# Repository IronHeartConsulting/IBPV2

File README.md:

IBPV2
=====

*DRAFT*

International Beacon Program - V2.0

http://www.ncdxf.org/pages/beacons.html
http://www.ncdxf.org/beacon/schematic.pdf
http://www.ncdxf.org/beacon/source.txt

The purpose of the NCDXF/IARU HF Beacon is to allow worldwide amateur
radio operators to judge HF propagation at your location, for your
local time.  To use it, tune in the beacons, and if you can hear a
beacon, you might be able to work some HF DX to that area of the
world.

The v1.0 beacon equipment consists of a HF Vertical antenna, Kenwood TS50
transceiver, a Trimble Acutime GPS unit, and a custom controller built
around a 8748 micro controller.

The network has been on the air for about 10 years. The current
problem is the equipment is getting old, and dying.  The original
designers never expected the units to remain in the field 10 years.

# HF V2.0 Beacon Network 

The goal is to design a replacement equipment package that duplicates
the existing features.  There has been a lot of proposals for more
features, other ways, etc.  But, none of those proposing have been
willing to put any work into it.

The aim is a practical design, with few or no new features.

# Equipment 

## Minimum Equipment
- ICOM IC-7200 Transceiver
- New TX Antenna
- GPS
- Switches
- LCD
- Rig Interface board
- Power Supply
- Filtering and isolation
- Chassis

## Additional possibilities
- Backup RTC with TXC (DS3231 or http://www.adafruit.com/products/255)
- Network: WiFi or Ethernet for command & control, status

# Functionality 

Each beacon transmits every three minutes, day and night.

A transmission consists of the callsign of the beacon sent at 22 words
per minute followed by four one-second dashes. The callsign and the
first dash are sent at 100 watts. The remaining dashes are sent at 10
watts, 1 watt and 100 milliwatts.

The beacons cycle thru the bands 14 Mhz, 18 MHz, 21 MHz, 24 MHz and 28 MHz.

Each station is given a specific time slot, such that only one
frequency is needed (on 20m, it’s 14.100).  The unit uses GPS to get
an accurate time, to synchronize it’s timeslot.  The beacon transmits
on each band for ten seconds, once every three minutes.

- Check switch for test sqeuence.
- Monitor the GPS unit - get the current time of day, and monitor the 1PPS signal.  
- Compute the correct timeslot for the station
- Check switches for band enable/disable.
- Send commands via  CI-V / CAT to the radio to select the frequency, and power level via commands
- Send the callsign and long dashes in CW.

This table gives the minute and second of the start of the first
transmission within the hour for each beacon on each frequency, and
reports the status.

http://www.ncdxf.org/beacon/beaconschedule.html

## Test Mode

Below is the v1.0 test mode

The test sequence is used for adjusting the power levels and checking
the keying waveforms.  Control the power level and request
either a string of dots or continual keying by using the switches
which normally disable particular bands:

| Effect    | Switch  |
| --------- | ------- |
| 100 watts | 28 MHz  |
| 10 watts  | 24 MHz  |
| 1 watt    | 21 MHz  |
| 0.1 watt  | 18 MHz  |
| Dits      | 14 MHz  |
| Carrier   | 10 MHz  |

# Equipment and Components Details 

## ICOM IC-7200 Transceiver

The ICOM IC-7200 transceiver offers CI-V commands for control of frequency, transmissions, and for monitoring.

For the CI-V commands see: http://www.plicht.de/ekki/civ/civ-p4.html

Statistics could also be gathered: for example, SWR could be measured.

## New TX Antenna

There is likely no impact of antenna choice on this part of the v2.0 beacon project.

## GPS

The GPS data stream will tell us the correct time of day.  Once we
know that, and our slot ID, we can just init a countdown register to
our time slot.

## Switches

The v1.0 system has the following switches:

- Band Switches (6)
- Test Switches (1 used, 3 reserved)

The band switches control which bands are used.  v1.0 covers 5 bands
with a 6th slot reserved for 10 MHz.

One test switch controls test mode, and in test mode, the band switches
have other functions.  Three other switches are reserved.

## LCD

The v1.0 system has a single LED for showing GPS and other status.

Switching to a small LCD character display will make operation easier
and will not greatly increase cost.  An i2c LCD is probably the best
choice.  

There are combination switch/LCD I2C products that we can use and
avoid the switch overloading by using screen feedback.  For example,
http://www.adafruit.com/products/772

Or we could use the Akafugu LCD backpack and use a separate mechanism for
switches.  This product has the advantage that it is mechanically easier
to mount in case.  https://store.akafugu.jp/products/26

## Arduino

- The Arduino Uno will be standard and remain easily understood for years.
- The Arduino Leonardo has the advantage of a separate programming port and hardware TTL port for the GPS.  Software TTL for CI-V rig control.
- The Arduino Mega has the disadvantage of being off the Arduino main line, and users often have trouble with support for hardware and libraries.
- The Arduino Yun is a combination of the Arduino Leonardo, a small Linux system running OpenWRT, and integrated Wifi connection, and an Ethernet connection.

Tentative Recommendations:
- The Arduino Leonardo is probably the best choice for the non-network version
- The Arduino Yun is the best choice for the connected version.

## Interface Board

The interface board is an Arduino Shield.  It has headers for
connections to the IC-7200 CI-V TTL serial, IC-7200 CW line, GPS TTL
serial, LCD, and possibly RTC.

## Optional item: Network: WiFi or Ethernet for command & control, status

The sites are mostly hosted.  If we had a USB connection to a local
PC, then we could send the host a file to load new code on the
controller, and we could also collect stats, etc.

If there is a network (WiFi or wired) we could also report the statistics,
such as whether it's online, what the SWR is.

## Optional item: Backup RTC with TXC

It might be nice to include a quartz crystal based time module, to
keep it disciplined with the GPS, in case there is some loss of GPS
signal.

Backup disciplined clock for use when GPS isn't available, for example, indoors.

- DS3231 board
- http://www.adafruit.com/products/255

# Engineering Resources 

- Project Management: Kevin K6TD
- Arduino system: Leigh WA5ZNU
- Rig Control: Kevin K6TD
- Beacon Event Loop: Leigh WA5ZNU
- UX: ?
- Systems Design: Kevin K6TD
- Hardware Design: Kevin K6TD
- Testing: ?

May 15, 2015
# libraries used
SoftSerial
AdaFruit_GPS
EnableInterrupt
LCDi2cNHD
arduinomorse

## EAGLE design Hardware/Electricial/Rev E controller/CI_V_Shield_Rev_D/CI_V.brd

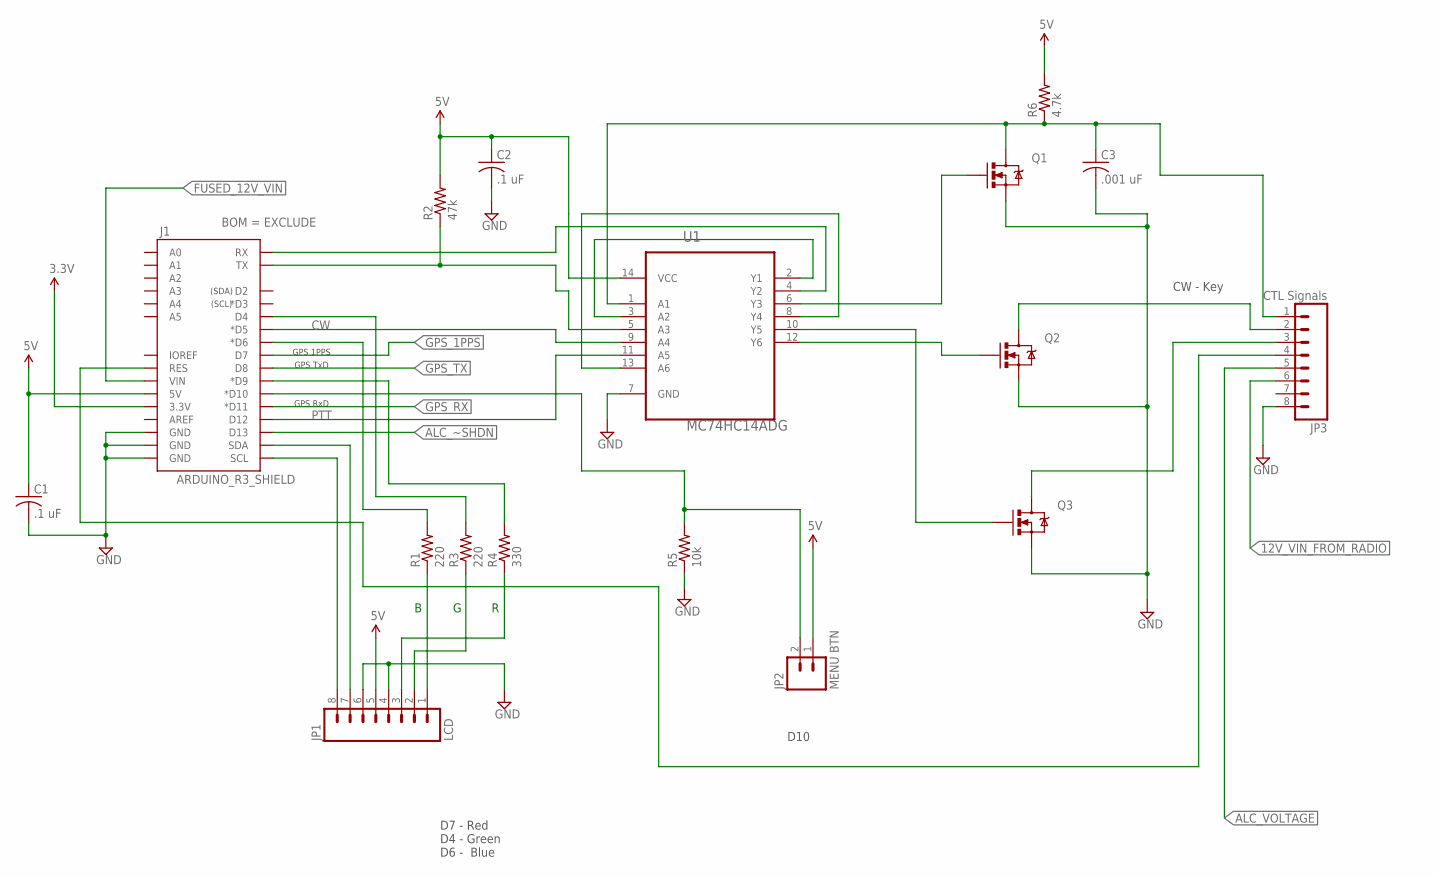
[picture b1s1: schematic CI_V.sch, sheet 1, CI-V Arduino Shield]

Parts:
C1, C2: .1 uF; C0805; PARTNO 120-0001-010
C3: .001 uF; C0805; PARTNO 120-0001-015
J1: ARDUINO_R3_SHIELD; UNO_R3_SHIELD
JP1: LCD; 1X08_PIN1_NO_SILK; PARTNO 125-0019-001
JP2: MENU BTN; 1X02; PARTNO 125-0019-001
JP3: CTL Signals; 1X08_PIN1_NO_SILK; PARTNO 125-0019-001
Q1, Q2, Q3: MOSFET-NCHANNELBSS123LT1G; SOT23-3; PARTNO 185-0001-001
R1, R3: 220; R0805; PARTNO 110-0001-010
R2: 47k; R0805; PARTNO 110-0001-030
R4: 330; R0805; PARTNO 110-0001-025
R5: 10k; R0805; PARTNO 110-0001-025
R6: 4.7k; R0805; PARTNO 110-0001-030
U1: MC74HC14ADG; SOIC127P600X175-14N; PARTNO 200-0001-001

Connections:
3.3V: J1.3.3V; also elsewhere on the board
5V: C1.1, C2.1, J1.5V, JP1.5, JP2.1, R2.2, R6.2, U1.14 (VCC); also elsewhere on the board
12V_VIN_FROM_RADIO: JP3.6; also elsewhere on the board
ALC_VOLTAGE: JP3.5; also elsewhere on the board
ALC_~SHDN: J1.D13; also elsewhere on the board
CW: J1.D5 (*D5), U1.9 (A4)
FUSED_12V_VIN: J1.VIN; also elsewhere on the board
GND: C1.2, C2.2, C3.2, J1.GND@0 (GND), J1.GND@1 (GND), J1.GND@2 (GND), JP1.4, JP1.6, JP3.8, Q1.2 (S), Q2.2 (S), Q3.2 (S), R5.1, U1.7 (GND); also elsewhere on the board
GPS_1PPS: J1.D7; also elsewhere on the board
GPS_RX: J1.D11 (*D11); also elsewhere on the board
GPS_TX: J1.D8; also elsewhere on the board
HARD_RX: J1.RX, U1.4 (Y2)
HARD_TX: J1.TX, R2.1, U1.5 (A3)
unnamed: C3.1, JP3.1, Q1.3 (D), R6.1, U1.1 (A1)
unnamed: JP3.2, Q2.3 (D)
unnamed: JP3.3, Q3.3 (D)
unnamed: Q1.1 (G), U1.6 (Y3)
unnamed: JP1.1, R1.1
unnamed: JP1.2, R3.1
unnamed: U1.2 (Y1), U1.3 (A2)
unnamed: Q2.1 (G), U1.12 (Y6)
unnamed: Q3.1 (G), U1.10 (Y5)
unnamed: J1.SCL, JP1.8
unnamed: U1.8 (Y4), U1.13 (A6)
unnamed: J1.SDA, JP1.7
unnamed: JP1.3, R4.1
unnamed: J1.D6 (*D6), R1.2
unnamed: J1.D4, R3.2
unnamed: J1.D9 (*D9), R4.2
unnamed: J1.D10 (*D10), JP2.2, R5.2
unnamed: J1.RES, JP3.4
PTT: J1.D12, U1.11 (A5)

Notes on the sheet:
CW - Key
D7 - Red D4 - Green D6 - Blue
D10
GPS TxD
GPS RxD
GPS 1PPS

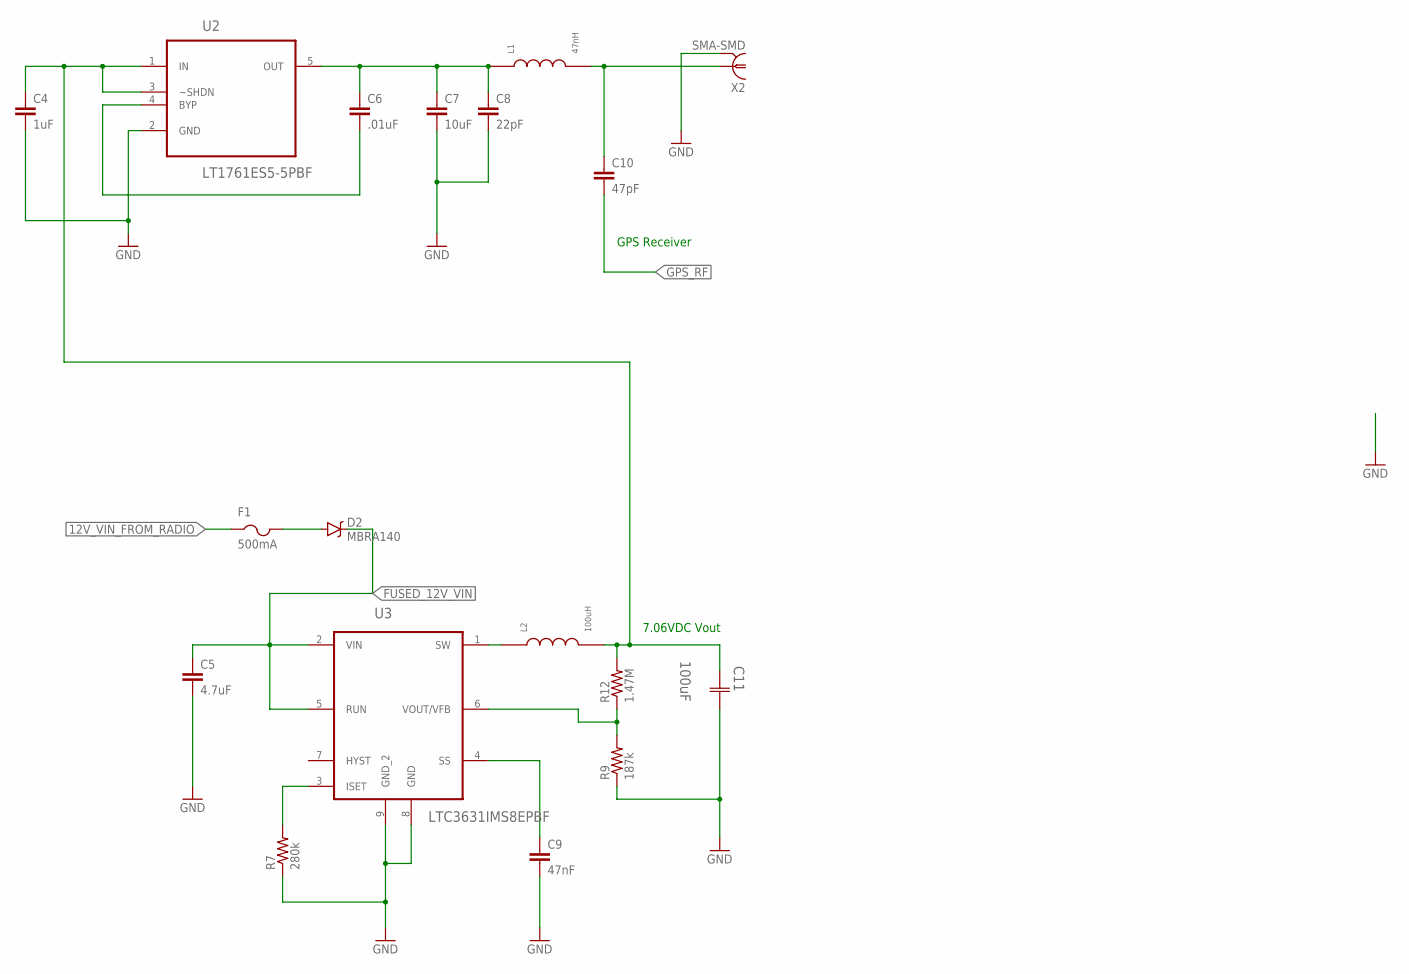
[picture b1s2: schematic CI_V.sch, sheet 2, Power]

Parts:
C4: 1uF; 0805; PARTNO 120-0001-015
C5: 4.7uF; 1210; PARTNO 120-0003-011
C6: .01uF; 0805; PARTNO 120-0001-020
C7: 10uF; 1210; PARTNO 120-0003-010
C8: 22pF; 0805; PARTNO 120-0004-011
C9: 47nF; 0805; PARTNO 120-0001-013
C10: 47pF; 0805; PARTNO 120-0004-010
C11: 100uF; CAPCP6032X280N; PARTNO 120-0005-050
D2: MBRA140; SMA-DIODE; PARTNO 140-0001-001
F1: 500mA; R1206; PARTNO 145-0001-001
L1: 47nH; 0805; PARTNO 155-0002-001
L2: 100uH; SLF7045; PARTNO 155-0001-001
R7: 280k; 0805; PARTNO 110-0002-015
R9: 187k; 0805; PARTNO 110-0002-020
R12: 1.47M; 0805; PARTNO 110-0002-010
U2: LT1761ES5-5PBF; SOT95P280X100-5N; PARTNO 230-0002-001
U3: LTC3631IMS8EPBF; SOP65P490X110-9N; PARTNO 230-0003-001
X2: SMA-SMD; PARTNO 125-0018-001

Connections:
7V_BUS: C4.1, C11.1 (C1), L2.2, R12.2, U2.1 (IN), U2.3 (~SHDN)
12V_VIN_FROM_RADIO: F1.1; also elsewhere on the board
FUSED_12V_VIN: C5.1, D2.C, U3.2 (VIN), U3.5 (RUN); also elsewhere on the board
GND: C4.2, C5.2, C7.2, C8.2, C9.2, C11.2 (C2), R7.1, R9.1, U2.2 (GND), U3.8 (GND), U3.9 (GND_2), X2.2@1 (2), X2.2@2 (2), X2.2@3 (2), X2.2@4 (2), X2.2@5 (2), X2.2@6 (2); also elsewhere on the board
GPS_RF: C10.2; also elsewhere on the board
ISET: R7.2, U3.3 (ISET)
unnamed: C10.1, L1.2, X2.1
unnamed: C6.2, U2.4 (BYP)
unnamed: D2.A, F1.2
SS: C9.1, U3.4 (SS)
SW: L2.1, U3.1 (SW)
VCC: C6.1, C7.1, C8.1, L1.1, U2.5 (OUT)
VFB: R9.2, R12.1, U3.6 (VOUT/VFB)

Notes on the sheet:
GPS Receiver
7.06VDC Vout

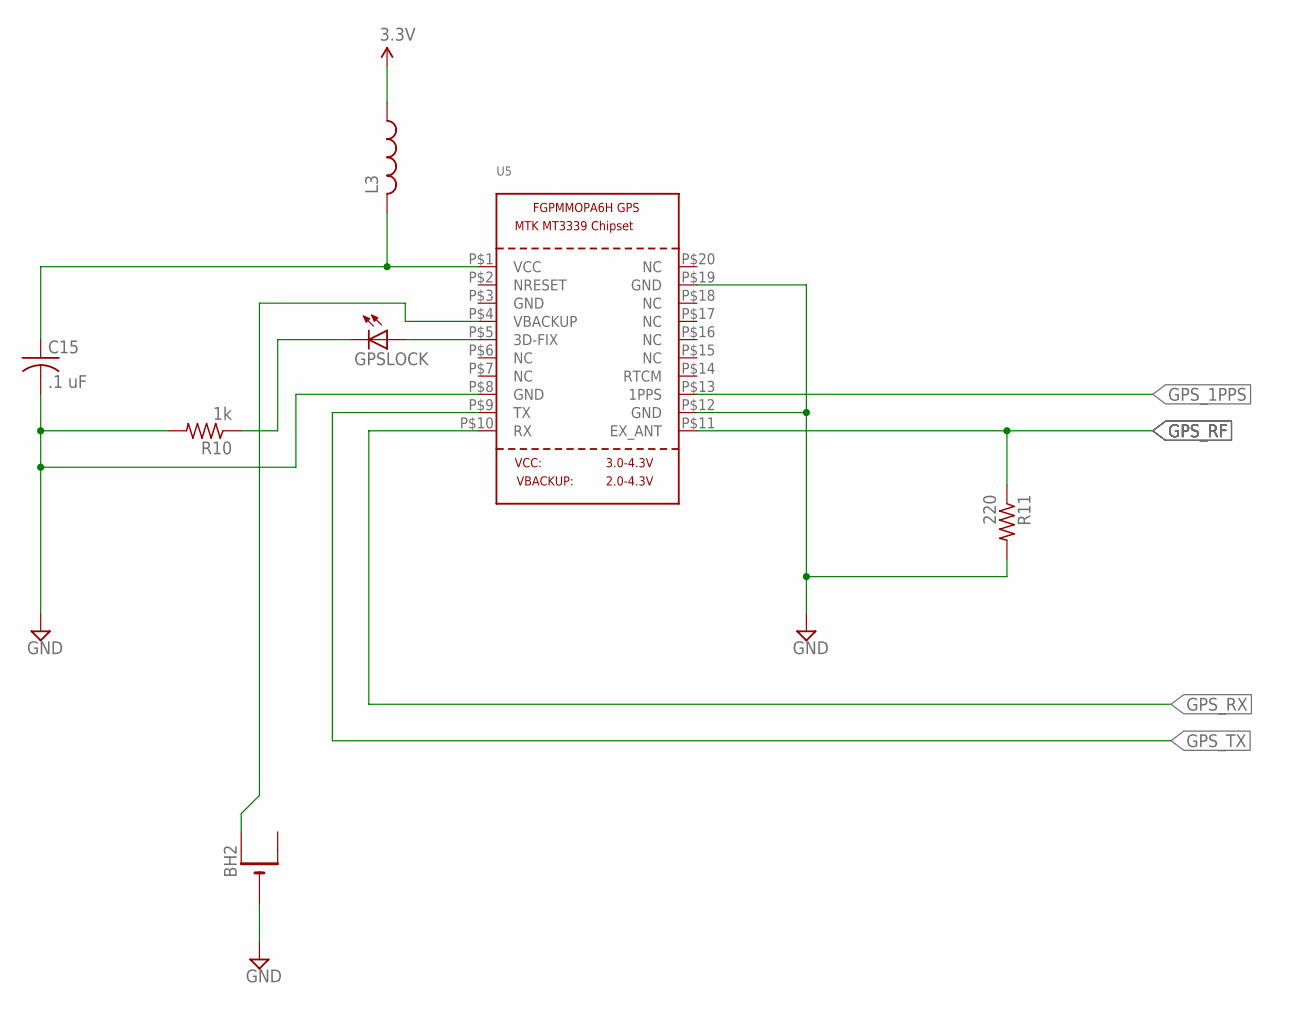
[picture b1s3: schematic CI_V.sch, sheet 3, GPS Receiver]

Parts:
BH2: CR1220SMT; CR1220-SMD; PARTNO 165-0001-001
C15: .1 uF; C0805; PARTNO 120-0001-010
GPSLOCK: LEDCHIPLED_0805; CHIPLED_0805; PARTNO 160-0007-001
L3: L-USL2012C; L2012C; PARTNO 155-0004-001
R10: 1k; R0805; PARTNO 110-0001-029
R11: 220; R0805; PARTNO 110-0001-010
U5: GPS_FGPMMOPA6H; FGPMMOPA6H; PARTNO 240-0001-001

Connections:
3.3V: L3.1; also elsewhere on the board
GND: BH2.-, C15.2, R10.2, R11.2, U5.P$8 (GND), U5.P$12 (GND), U5.P$19 (GND); also elsewhere on the board
GPS_1PPS: U5.P$13 (1PPS); also elsewhere on the board
GPS_BATT: BH2.+$1 (+), U5.P$4 (VBACKUP)
GPS_RF: R11.1, U5.P$11 (EX_ANT); also elsewhere on the board
GPS_RX: U5.P$10 (RX); also elsewhere on the board
GPS_TX: U5.P$9 (TX); also elsewhere on the board
unnamed: C15.1, L3.2, U5.P$1 (VCC)
unnamed: GPSLOCK.A, U5.P$5 (3D-FIX)
unnamed: GPSLOCK.C, R10.1

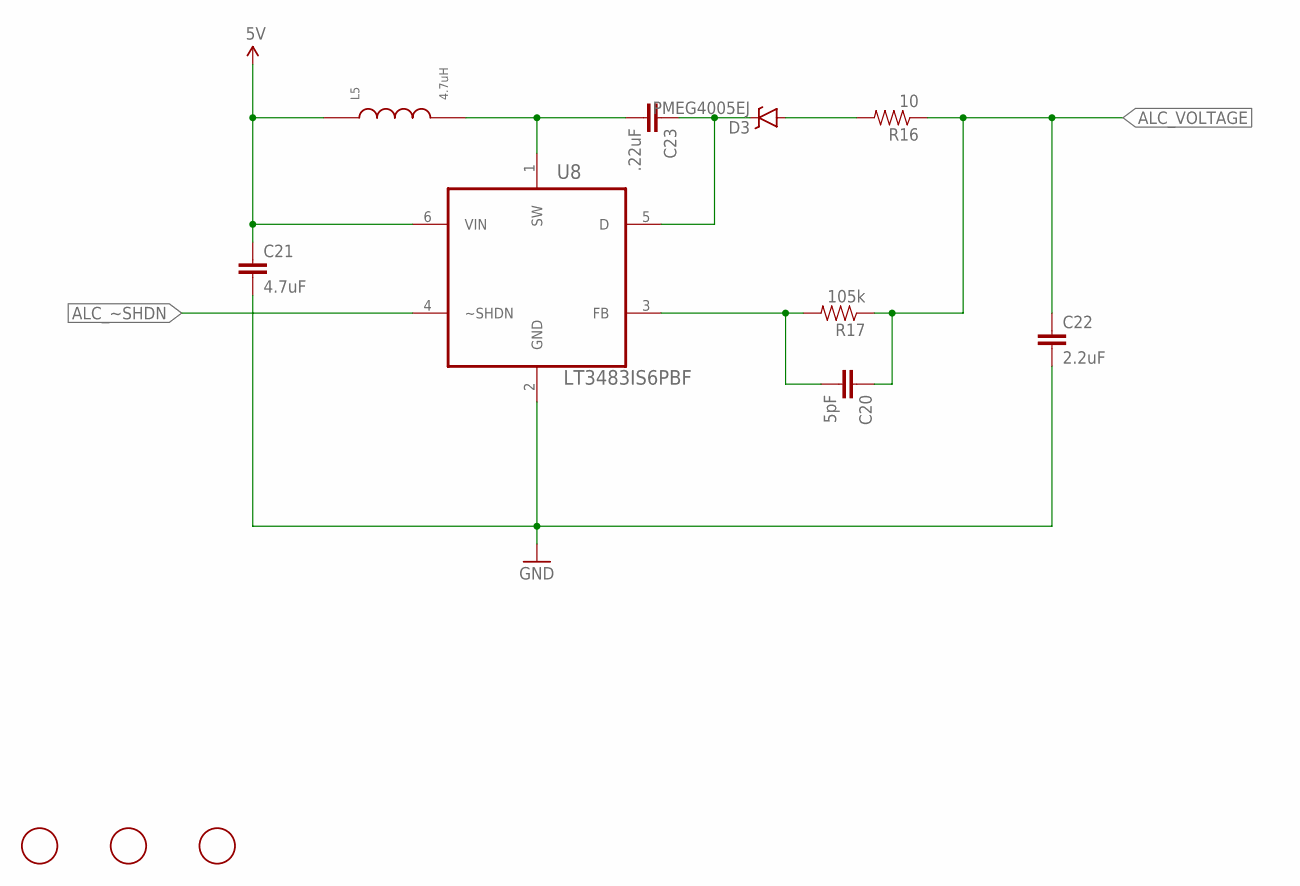
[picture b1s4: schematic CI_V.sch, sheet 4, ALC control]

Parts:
C20: 5pF; 0805; PARTNO 120-0004-010
C21: 4.7uF; 1210; PARTNO 120-0003-011
C22: 2.2uF; 0805; PARTNO 120-0002-011
C23: .22uF; 0805; PARTNO 120-0001-022
D3: PMEG4005EJ; SOD-323; PARTNO 140-0002-001
L5: 4.7uH; 0805; PARTNO 155-0003-001
R16: 10; 0805; PARTNO 110-0001-027
R17: 105k; 0805; PARTNO 110-0003-010
U8: LT3483IS6PBF; SOT95P280X100-6N
U$1, U$6, U$7: FIDUCIAL; FIDUCIAL_1MM

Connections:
5V: C21.1, L5.1, U8.6 (VIN); also elsewhere on the board
ALC_VOLTAGE: C20.1, C22.1, R16.1, R17.1; also elsewhere on the board
ALC_~SHDN: U8.4 (~SHDN); also elsewhere on the board
GND: C21.2, C22.2, U8.2 (GND); also elsewhere on the board
unnamed: D3.A, R16.2
unnamed: C23.2, L5.2, U8.1 (SW)
unnamed: C23.1, D3.C, U8.5 (D)
unnamed: C20.2, R17.2, U8.3 (FB)

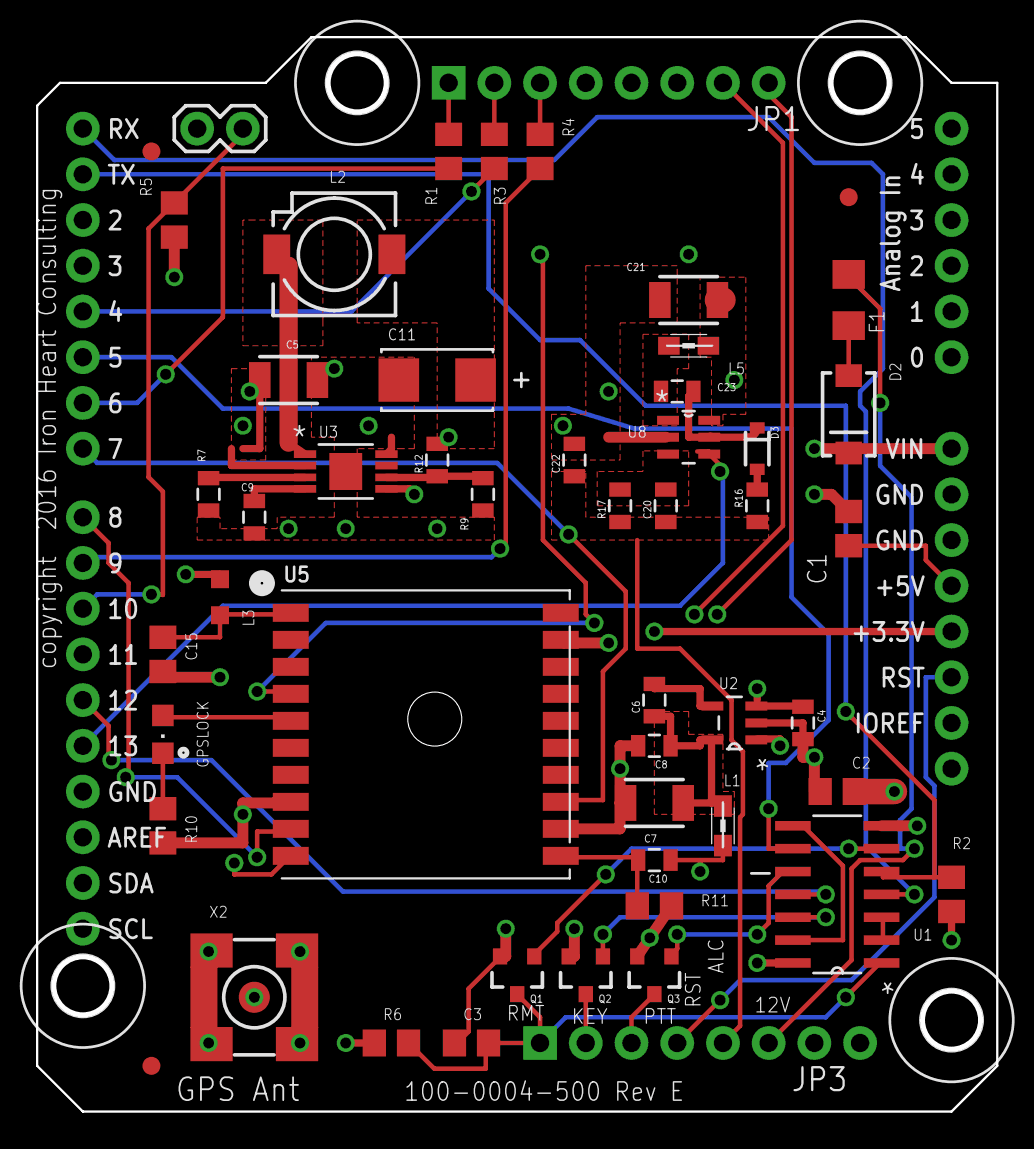
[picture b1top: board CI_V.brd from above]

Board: 4 copper layers, 53.3 x 59.7 mm, 58 parts (1 on the bottom side), 50 nets.

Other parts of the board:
U$2, U$3, U$4, U$5: 3,2

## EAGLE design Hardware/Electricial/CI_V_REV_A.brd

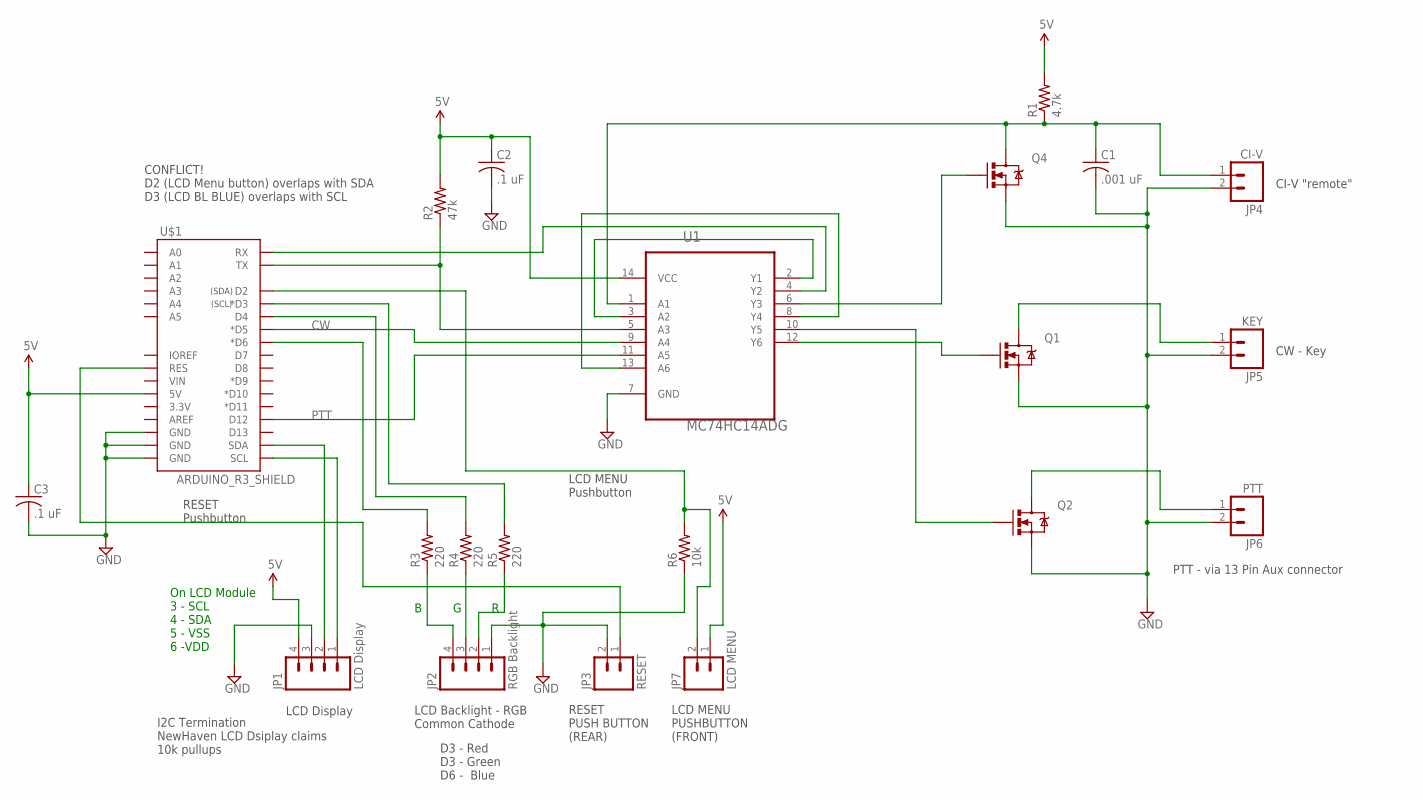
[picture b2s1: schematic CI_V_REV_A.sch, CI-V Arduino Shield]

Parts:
C1: .001 uF; C0805
C2, C3: .1 uF; C0805
JP1: LCD Display; 1X04
JP2: RGB Backlight; 1X04
JP3: RESET; 1X02
JP4: CI-V; 1X02
JP5: KEY; 1X02
JP6: PTT; 1X02
JP7: LCD MENU; 1X02
Q1, Q2, Q4: MOSFET-NCHANNELBSS123LT1G; SOT23-3
R1: 4.7k; R0805
R2: 47k; R0805
R3, R4, R5: 220; R0805
R6: 10k; R0805
U1: MC74HC14ADG; SOIC127P600X175-14N
U$1: ARDUINO_R3_SHIELD; UNO_R3_SHIELD

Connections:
5V: C2.1, C3.1, JP1.4, JP7.1, R1.2, R2.2, U1.14 (VCC), U$1.5V
CW: U1.9 (A4), U$1.D5 (*D5)
GND: C1.2, C2.2, C3.2, JP1.3, JP2.1, JP3.2, JP4.2, JP5.2, JP6.2, Q1.2 (S), Q2.2 (S), Q4.2 (S), R6.1, U1.7 (GND), U$1.GND@0 (GND), U$1.GND@1 (GND), U$1.GND@2 (GND)
HARD_RX: U1.4 (Y2), U$1.RX
HARD_TX: R2.1, U1.5 (A3), U$1.TX
unnamed: C1.1, JP4.1, Q4.3 (D), R1.1, U1.1 (A1)
unnamed: JP5.1, Q1.3 (D)
unnamed: JP6.1, Q2.3 (D)
unnamed: Q4.1 (G), U1.6 (Y3)
unnamed: JP2.4, R3.1
unnamed: JP2.3, R4.1
unnamed: U1.2 (Y1), U1.3 (A2)
unnamed: Q1.1 (G), U1.12 (Y6)
unnamed: Q2.1 (G), U1.10 (Y5)
unnamed: JP1.1, U$1.SCL
unnamed: U1.8 (Y4), U1.13 (A6)
unnamed: JP1.2, U$1.SDA
unnamed: JP2.2, R5.1
unnamed: R3.2, U$1.D6 (*D6)
unnamed: R4.2, U$1.D4
unnamed: R5.2, U$1.D3 (*D3)
unnamed: JP7.2, R6.2, U$1.D2
unnamed: JP3.1, U$1.RES
PTT: U1.11 (A5), U$1.D12

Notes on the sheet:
CI-V "remote"
CW - Key
PTT - via 13 Pin Aux connector
I2C Termination NewHaven LCD Dsiplay claims 10k pullups
LCD Display
LCD Backlight - RGB Common Cathode
On LCD Module 3 - SCL 4 - SDA 5 - VSS 6 -VDD
RESET PUSH BUTTON (REAR)
LCD MENU PUSHBUTTON (FRONT)
RESET Pushbutton
LCD MENU Pushbutton
D3 - Red D3 - Green D6 - Blue
CONFLICT! D2 (LCD Menu button) overlaps with SDA D3 (LCD BL BLUE) overlaps with SCL

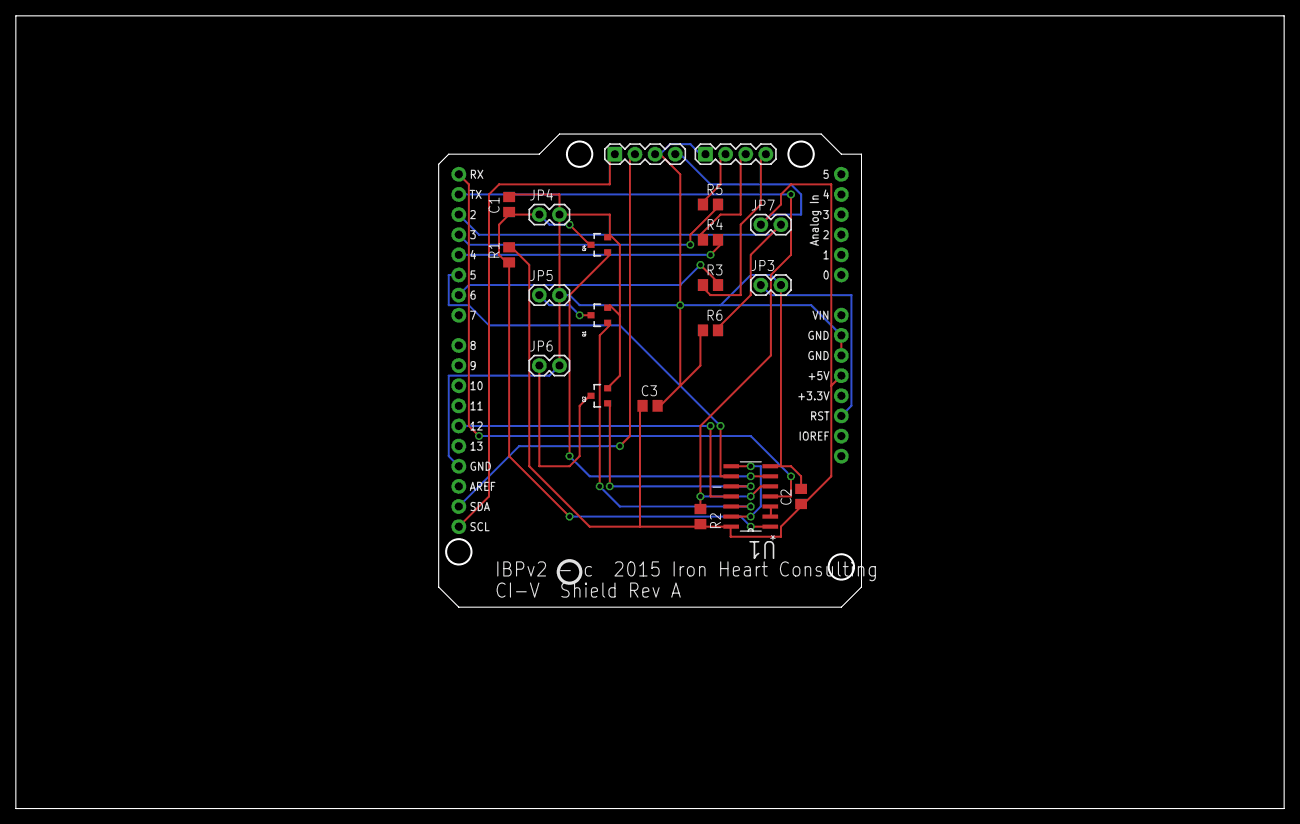
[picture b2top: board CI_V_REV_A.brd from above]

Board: 2 copper layers, 160.0 x 100.0 mm, 21 parts (0 on the bottom side), 24 nets.

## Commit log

2014-07-23 Added draft design text to README.md
2014-07-23 Add references directory with critical documents (schematic, source code) from v1.0 project
2014-07-24 Add test mode, switches, LED replaced by LCD
2014-07-24 add data sheets for GPS unit and IC-7200
2014-07-24 Add switch/CD reocmmendations.
2014-07-24 describe Akafugu advantage for LCD
2014-08-27 Added IC-7200 Service manual
    Factory direct, full service manual for the IC-7200 HF transceiver
2014-08-31 Added CIV library straight from K6UM SVN. Doesn't work. Changes coming.
2014-09-01 added start of debugging class
2014-09-01 Move location of exmaple code
2014-09-03 Compiles
2014-09-03 Runs...debug flag doesn't work
2014-09-04 Debugging output for BCD covnersion
2014-09-12 CIV talks to radio.
2014-09-12 Fixed debug flags
2014-09-13 working
2014-10-02 Update project responsibilities for more finer-grained list of software
2014-10-02 add requirements.txt list of URLs of third-party libraries required to build
2015-04-30 catch up the repository
2015-05-01 add WA5ZNU's code to repo, clean out unrelated files
2015-05-01 add back in the correct version of Leigh's code
2015-05-12 added Rev A schematics; updated LCD testing sketch
2015-05-12 converted BCNDebug library to 1.5 format
2015-05-12 converted CI-V library to V1.5 format
2015-05-12 added more files to exclude
2015-05-13 added GPS test sketches
2015-05-14 1PP interrupt testing
2015-05-14 exclude some libraries
2015-05-16 add'l test for GPS
2015-05-19 working out 1PS interrupt conflict
2015-05-22 more library comments updates
2015-05-22 more libraries not to store in repo
2015-05-28 local SoftwareSerial - start of fix interrupts
2015-06-03 working on interrupts
2015-06-05 more test code
2015-06-15 updates from debugging
2015-06-15 Tiny GPS copy of beacon files (Nov 10, WA5ZNU)
2015-06-15 merged changes from old veriosn of beacon code
2015-06-16 merged in and tested code from 11/10. Largely works
2015-06-16 deleted adafruit GPS lib - using TInyGPS instead
2015-06-16 bug fixes. Long DAH keying, frequency, and callsign in lower case
2015-06-16 added debug output samples
2015-06-17 fixed: no TX during CW ID
2015-06-18 flash the backlight for mode changes, add descriptive text
2015-06-19 more text on LCD Displays
2015-06-19 add libraries
2015-06-19 move libraries to correct sub-dir
2015-06-19 LCD wiring ECO docs
2015-06-20 FP LCD now working. ECO needed for RED baclight
2015-06-23 fixed LED during ID transmisison
2015-06-24 Proposed fix to CW ID stutter.Eliminate interrupts generated by gps_serial by calling stopListening() and listen() around its use. Start off with stopListening().
2015-06-24 EEPROM layout document - simple text
2015-06-29 tested and on the air, albeit with a few bug reports
2015-06-29 added various debug and testing files
2015-06-29 changed station callsigns to lower case. Expected by morse code routine. Added test for no GPS fix
2015-06-29 added 20dBm/100 mW case statement
2015-06-29 forgot the actaully change the power level
2015-06-30 fix 18m frequency, fix powe rsetting for 20dBm, library category, so IDE shuts up
2015-07-01 debug code for missing last dash; fixed GPS DO
2015-07-01 ISSUE-12: Make Serial Debug Print OptionalCannot test compile due to ISSUE-5 missing arduinomorse.
2015-07-01 remove sprintf from schedule.ino. Issue-13
2015-07-02 complete testing of debug print - ISSUE-12
2015-07-06 modified schedule loop to use direct delay, and place 1st long dash right after callsign. Some file cleanup too
2015-07-08 fixed CW ID power on higher bands
2015-07-11 move to other side of 1PPS tick; inserted delay before start of CW ID - calibrated ot FAROS
2015-07-11 W6WX trial setup
2015-07-15 various items needs to remote loading
2015-07-19 GPS echo test skethc added. Works with our pinout
2015-07-29 working leo reset now. Populate and make work on a BBB
2015-07-30 add release directory and updte Makefiles
2015-07-30 changed avrdude verbosity to -q
2016-01-02 Added BOM for power injector stored copy of beacon list from faros updated debug and version
2016-01-07 Beacon.lst file for test beacons at Kevin's house
2016-01-17 added docs for KH6RS installation added KH6RS to stations file
2016-01-17 FAROS beacon file from VE3NEA with updates for KH6RS and other moves as noted by N6TV readme file detailing installation.
2016-02-02 add mode to let radio listen to 20M PSK31 when idle
2016-06-01 Added IC-7300 documentation added power control testing info fixed LCD display dropped characters - decreased I2C bus speed to 50KHz Tested with Rev B controller changed station selection to be a #de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
2016-06-16 added spreadsheet looking at poer level control ideas
2016-06-16 spreadsheet for tracking power control ideas
2016-07-18 add radio test software with CLI; station selection now done in config file as an index; spreadsheet for TX power calcs.
2016-08-01 testing Rev C PCBA
2016-09-22 catchup
2016-09-22 add Rev B mechanical models
2016-10-11 add eeprom util, labels, read slot ID from EEPROM, update for VE8AT deployment
2016-10-11 change LCD I2C freq back to 100kHz. 2X delay may affect TX loop performance
2016-10-13 put I2C back to 50kHz, reduce delay to start of TX to 134
2016-12-07 menu handling
2016-12-15 bug fixes
2016-12-21 V2.9 release
2016-12-27 fixed menu selection for timeslot
2016-12-27 remove Excel backup file
2016-12-28 fixed radio init, more menu fixes, spelling errors. V2.11
2016-12-29 debugging around CW timing
2017-02-01 added hex file, and checksum of hex file
2017-02-02 fixed power. version still 2.7c
2017-02-03 fixed schedule loop to roll over at 170->0 when slot falls across this boundary. V2.7D
2017-02-05 V2.7e. if wall_ticks changes, then restart search for timeslot; move setup to -1 second; move radio prep to correct places; adjust delay at start of beacon - tuned for FAROS
2017-02-13 code clean up. added SKIP menu item
2017-02-17 start of V2.8. Added eeprom util to console code. take loop delay from eeprom.
2017-02-18 programming manual updated
2017-02-20 minor edits to v2.8b.
2017-02-27 clean up LCD display. fix rig setup regression. LCD changes cause delay new vlaue ot be 468
2017-03-03 fix compile issues for 1.8.1 - compiles, but, doesn't run
2017-03-05 V2.8D. Changing CW timing, per N6TV.
2017-03-27 update CW timing, add analog pins as debug outputs
2017-10-16 catch up
2017-10-19 reset once every 24 hours
2020-03-18 new version

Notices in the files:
Hardware/Electricial/Rev E controller/CI_V_Shield_Rev_D/CI_V.brd:
copyright  2016 Iron Heart Consulting
parts and their libraries:
SparkFun-DiscreteSemi: Licensing: Creative Commons ShareAlike 4.0 International - https://creativecommons.org/licenses/by-sa/4.0
